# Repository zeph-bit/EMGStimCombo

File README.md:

# EMGStimCombo
Stackable sEMG and TENS combination device.

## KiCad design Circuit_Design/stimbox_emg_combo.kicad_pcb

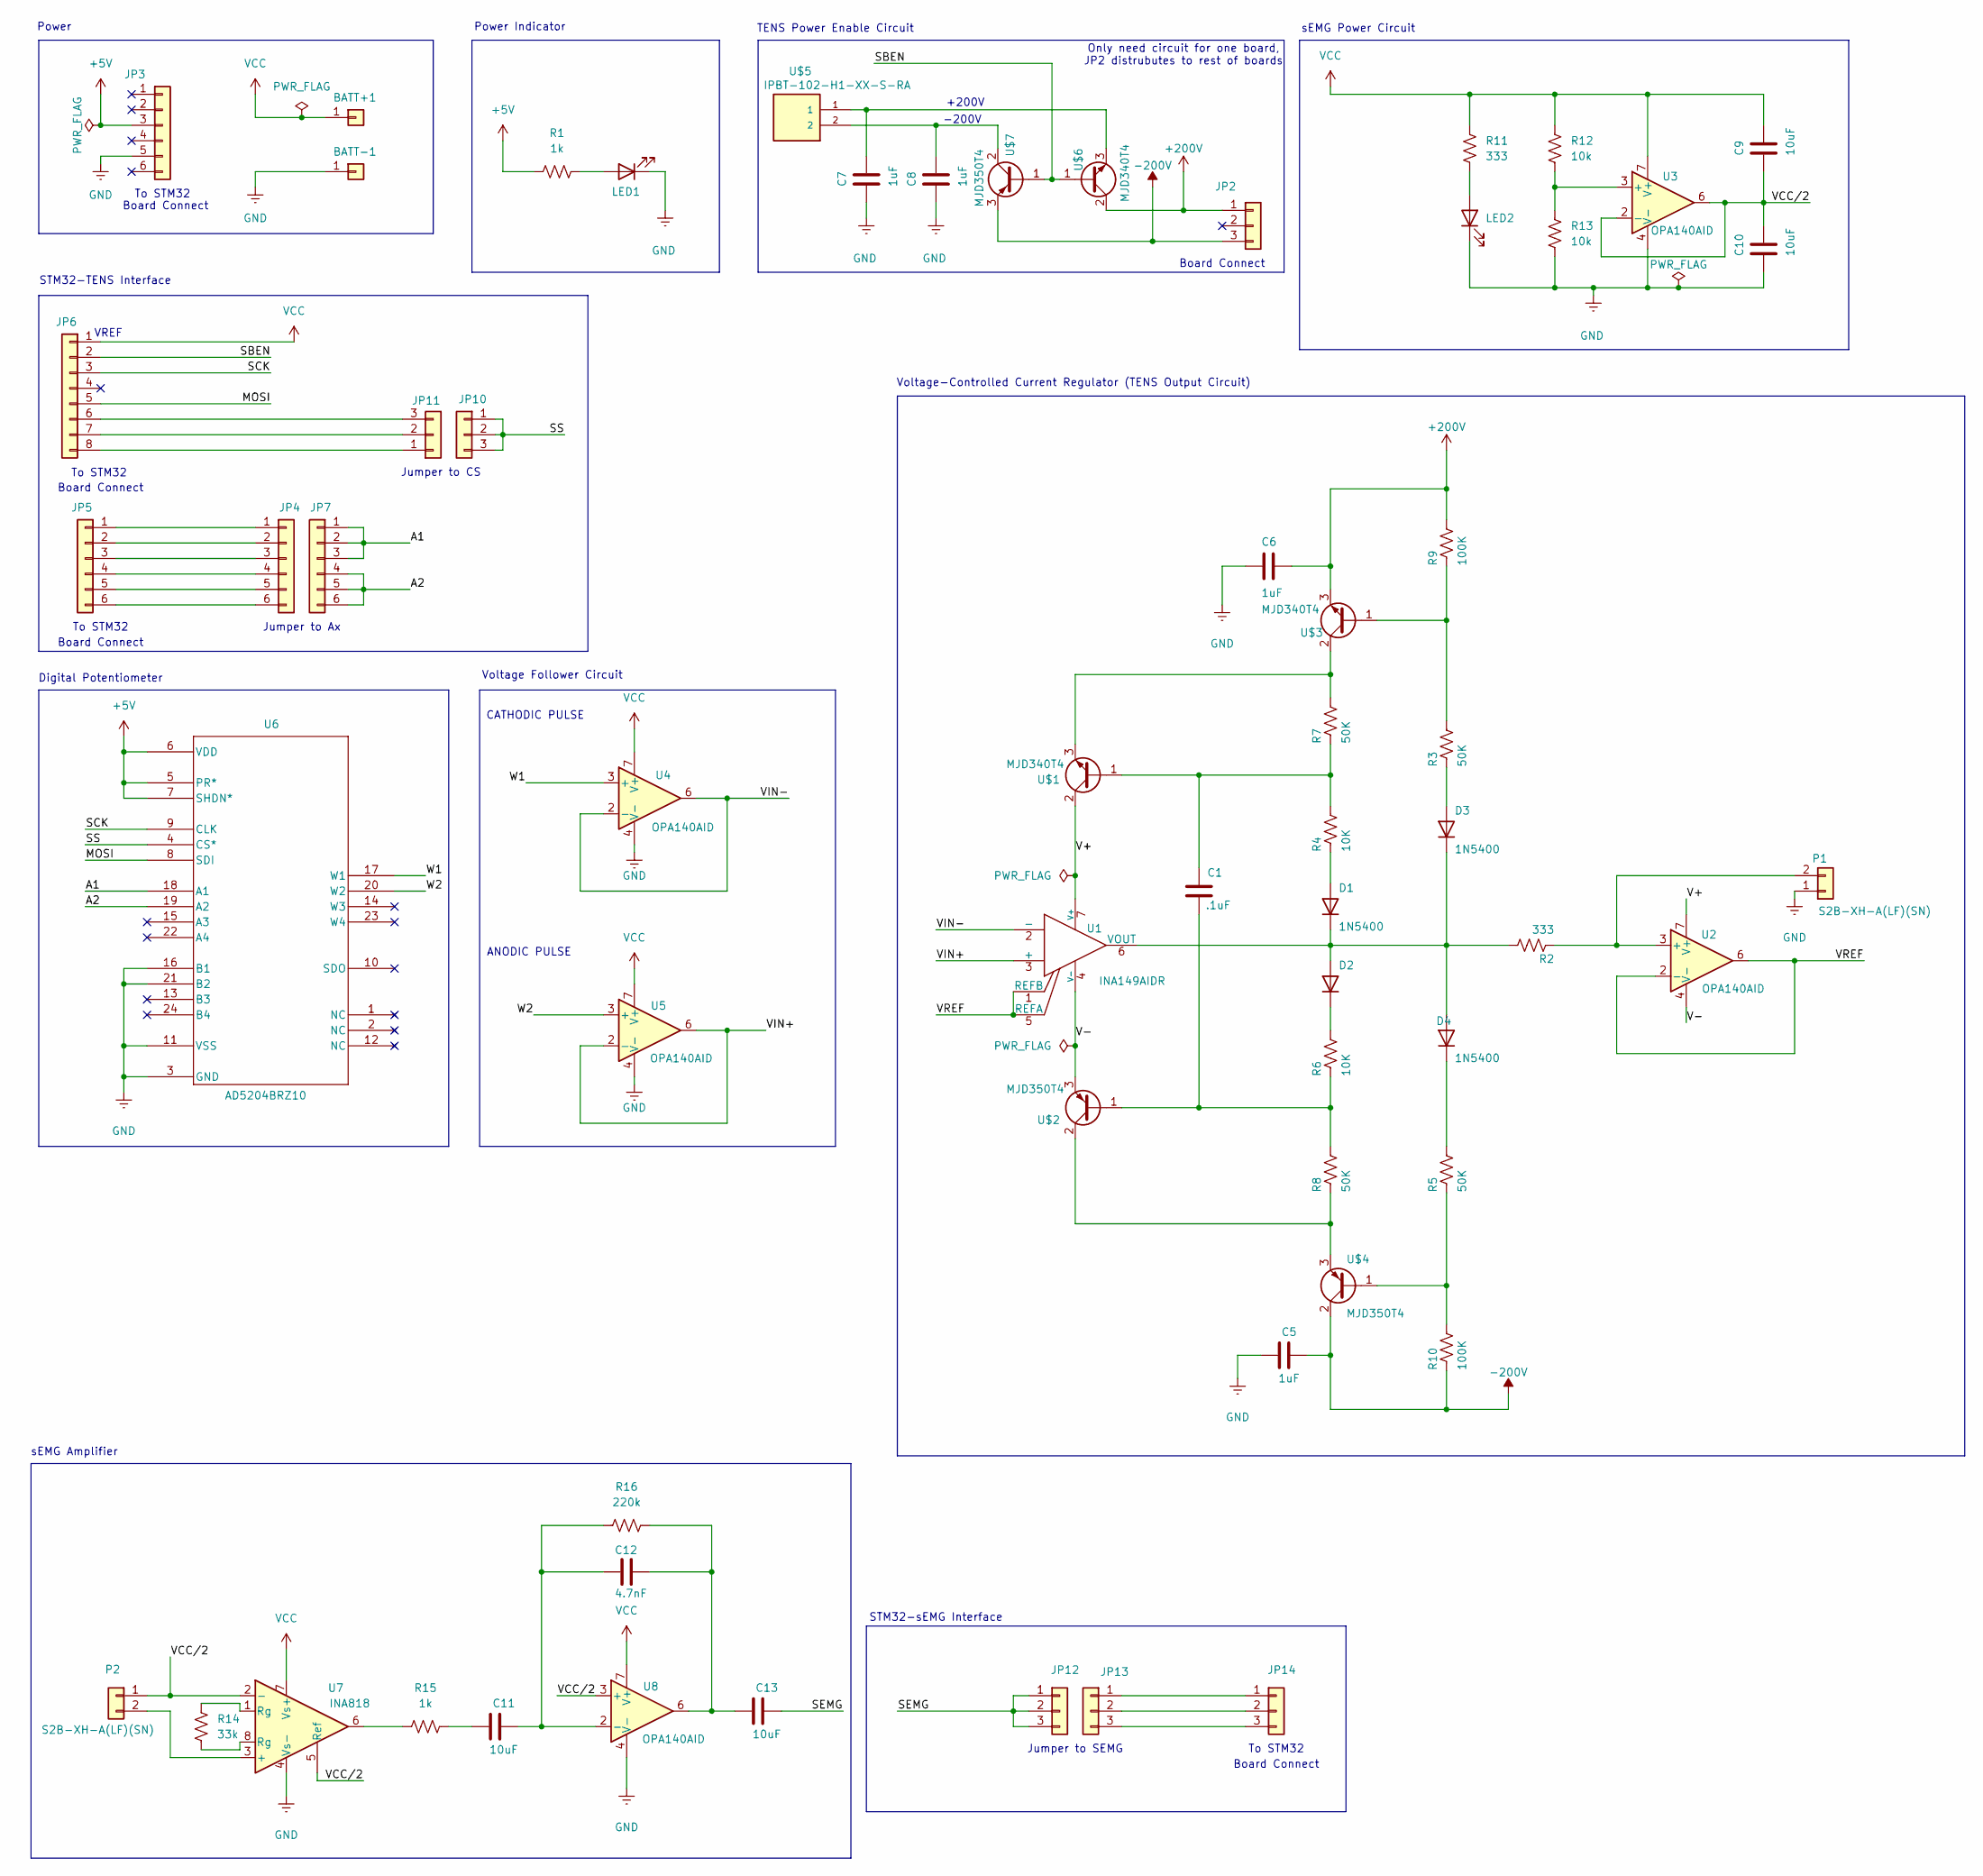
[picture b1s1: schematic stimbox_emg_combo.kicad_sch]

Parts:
BATT+1: PINHD-1X1; PinHeader_1x01_P2.54mm_Vertical
BATT-1: PINHD-1X1; PinHeader_1x01_P2.54mm_Vertical
C1: .1uF; C_1206_3216Metric
C5, C6, C7, C8: 1uF; C_2220_5750Metric
C9, C10, C11, C13: 10uF; C_2220_5750Metric
C12: 4.7nF; C_2220_5750Metric
D1, D2, D3, D4: 1N5400; D_DO-201AD_P15.24mm_Horizontal
JP2, JP14: PINHD-1X3-STACK; PinSocket_1x03_P2.54mm_Vertical
JP3: PINHD-1X6-STACK; PinSocket_1x02_P2.54mm_Vertical
JP4, JP7: PINHD-1X6; PinHeader_1x06_P2.54mm_Vertical
JP5: PINHD-1X6-STACK; PinSocket_1x06_P2.54mm_Vertical
JP6: PINHD-1X8-STACK; PinSocket_1x08_P2.54mm_Vertical
JP10, JP11, JP12, JP13: PINHD-1X3; PinHeader_1x03_P2.54mm_Vertical
LED1, LED2: LEDCHIPLED_1206; LED_1206_3216Metric
P1, P2: S2B-XH-A(LF)(SN); JST_XH_S2B-XH-A_1x02_P2.50mm_Horizontal; DIGI-KEY_PART_NUMBER 455-2257-ND
R1, R15: 1k; R_0805_2012Metric
R2, R11: 333; R_1206_3216Metric
R3, R5, R7, R8: 50K; R_1206_3216Metric
R4, R6: 10K; R_1206_3216Metric
R9, R10: 100K; R_1206_3216Metric
R12, R13: 10k; R_1206_3216Metric
R14: 33k; R_1206_3216Metric
R16: 220k; R_1206_3216Metric
U1: INA149AIDR; D0008A_L
U2, U3, U4, U5, U8: OPA140AID; SOIC-8_3.9x4.9mm_P1.27mm
U6: AD5204BRZ10; RW_24_ADI; DIGI-KEY_PART_NUMBER AD5204BRZ100-ND
U7: INA818; SOIC-8_TEX
U$1, U$3, U$6: MJD340T4; TO-252_6P6X6P2X2P25_STM
U$2, U$4, U$7: MJD350T4; TO-252_6P6X6P2X2P25_STM
U$5: IPBT-102-H1-XX-S-RA

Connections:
+3.3V: JP3.2
+5V: JP3.3, R1.1, U6.5 (PR*), U6.6 (VDD), U6.7 (SHDN*)
/A1: JP7.1, JP7.2, JP7.3, U6.18 (A1)
/A2: JP7.4, JP7.5, JP7.6, U6.19 (A2)
/MOSI: JP6.5, U6.8 (SDI)
/SBEN: JP6.2, U$6.1 (B), U$7.1 (B)
/SCK: JP6.3, U6.9 (CLK)
/SEMG: C13.2, JP12.1, JP12.2, JP12.3
/SS: JP10.1, JP10.2, JP10.3, U6.4 (CS*)
/V+: U1.7 (V+), U2.7 (V+), U$1.2 (C)
/V-: U1.4 (V-), U2.4 (V-), U$2.3 (E)
/VCC/2: C9.1, C10.2, P2.1, U3.2 (-), U3.6, U7.2 (-), U7.5 (Ref), U8.3 (+)
/VIN+: U1.3 (+), U5.2 (-), U5.6
/VIN-: U1.2 (-), U4.2 (-), U4.6
/VREF: U1.1 (REFB), U1.5 (REFA), U2.2 (-), U2.6
/W1: U4.3 (+), U6.17 (W1)
/W2: U5.3 (+), U6.20 (W2)
GND: BATT-1.1 (Pin_1_1), C5.1, C6.1, C7.1, C8.1, C10.1, JP3.5, LED1.1 (K), LED2.1 (K), P1.1, R13.2, U3.4 (V-), U4.4 (V-), U5.4 (V-), U6.3 (GND), U6.11 (VSS), U6.16 (B1), U6.21 (B2), U7.4 (Vs-), U8.4 (V-)
unnamed: C11.1, R15.2
unnamed: C12.2, C13.1, R16.2, U8.6
unnamed: D1.2 (A), R4.2
unnamed: D1.1 (K), D2.2 (A), D3.1 (K), D4.2 (A), R2.1, U1.6 (VOUT)
unnamed: D2.1 (K), R6.1
unnamed: D3.2 (A), R3.2
unnamed: D4.1 (K), R5.1
unnamed: JP4.1, JP5.1
unnamed: JP4.2, JP5.2
unnamed: JP4.3, JP5.3
unnamed: JP4.4, JP5.4
unnamed: JP4.5, JP5.5
unnamed: JP4.6, JP5.6
unnamed: JP6.8, JP11.1
unnamed: JP6.7, JP11.2
unnamed: JP6.6, JP11.3
unnamed: JP13.1, JP14.1
unnamed: JP13.2, JP14.2
unnamed: JP13.3, JP14.3
unnamed: LED1.2 (A), R1.2
unnamed: LED2.2 (A), R11.2
unnamed: P1.2, R2.2, U2.3 (+)
unnamed: P2.2, U7.3 (+)
unnamed: R14.1, U7.1 (Rg)
unnamed: R14.2, U7.8 (Rg)
unnamed: R15.1, U7.6
unnamed: R12.2, R13.1, U3.3 (+)
unnamed: C11.2, C12.1, R16.1, U8.2 (-)
unnamed: C1.1, R4.1, R7.2, U$1.1 (B)
unnamed: R7.1, U$1.3 (E), U$3.2 (C)
unnamed: C1.2, R6.2, R8.1, U$2.1 (B)
unnamed: R8.2, U$2.2 (C), U$4.3 (E)
unnamed: R3.1, R9.2, U$3.1 (B)
unnamed: R5.2, R10.1, U$4.1 (B)
unnamed: C7.2, U$5.1, U$6.3 (E)
unnamed: C8.2, U$5.2, U$7.2 (C)
VCC: BATT+1.1 (Pin_1_1), C9.2, JP6.1, R11.1, R12.1, U3.7 (V+), U4.7 (V+), U5.7 (V+), U7.7 (Vs+), U8.7 (V+)

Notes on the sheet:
To STM32
Only need circuit for one board, JP2 distrubutes to rest of boards
Board Connect
Jumper to SEMG
STM32-sEMG Interface
TENS Power Enable Circuit
Jumper to CS
-200V
Jumper to Ax
+200V
VREF
sEMG Power Circuit
Power
Voltage Follower Circuit
ANODIC PULSE
Voltage-Controlled Current Regulator (TENS Output Circuit)
sEMG Amplifier
CATHODIC PULSE
Digital Potentiometer
Power Indicator
STM32-TENS Interface

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
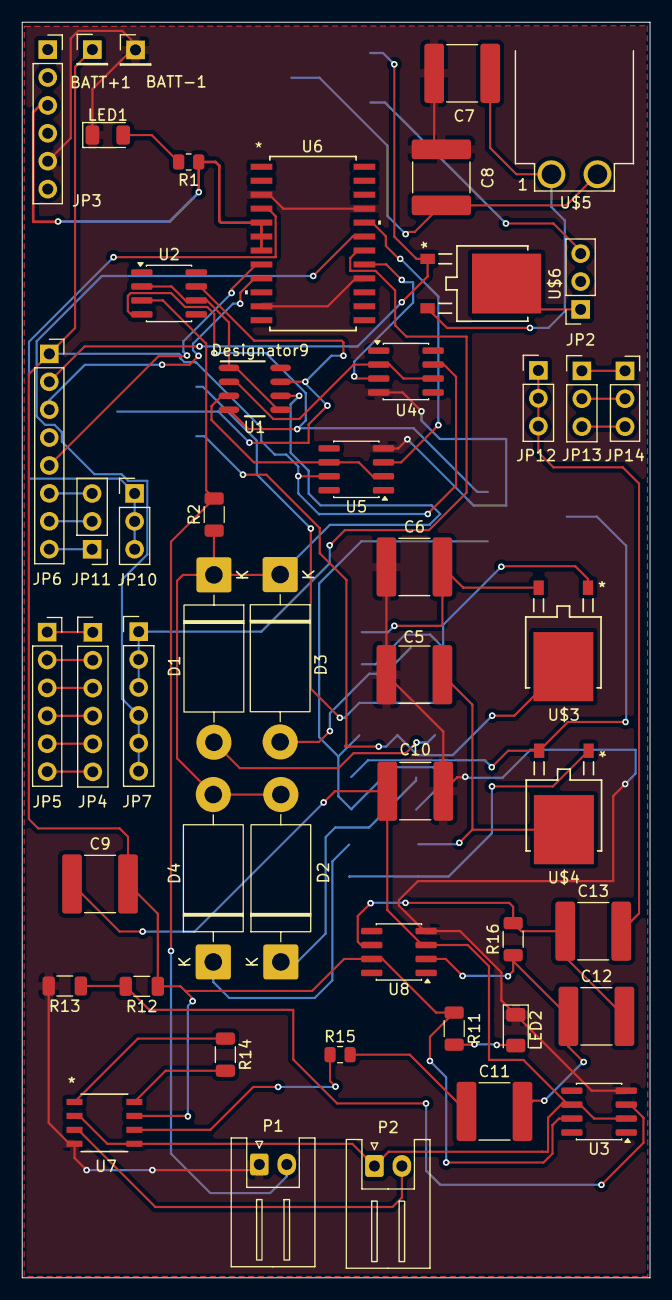
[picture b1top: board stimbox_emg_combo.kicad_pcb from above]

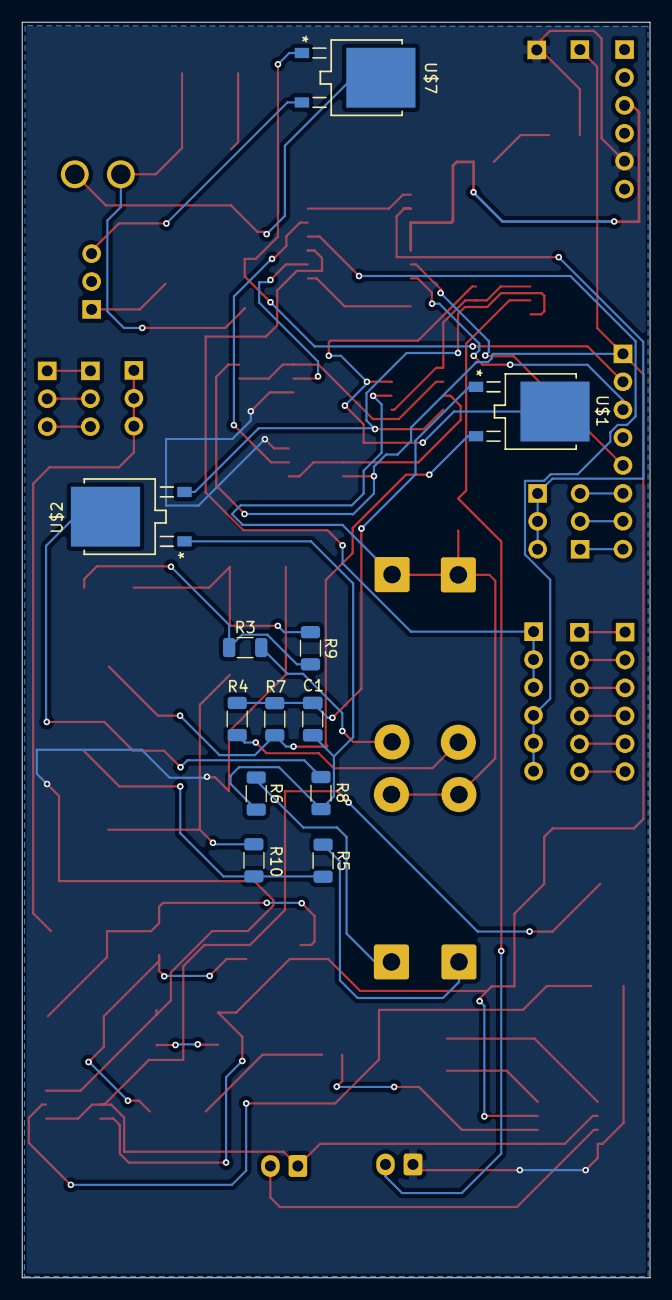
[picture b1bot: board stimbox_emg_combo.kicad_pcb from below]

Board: 2 copper layers, 57.2 x 114.3 mm, 62 parts (12 on the bottom side), 58 nets.

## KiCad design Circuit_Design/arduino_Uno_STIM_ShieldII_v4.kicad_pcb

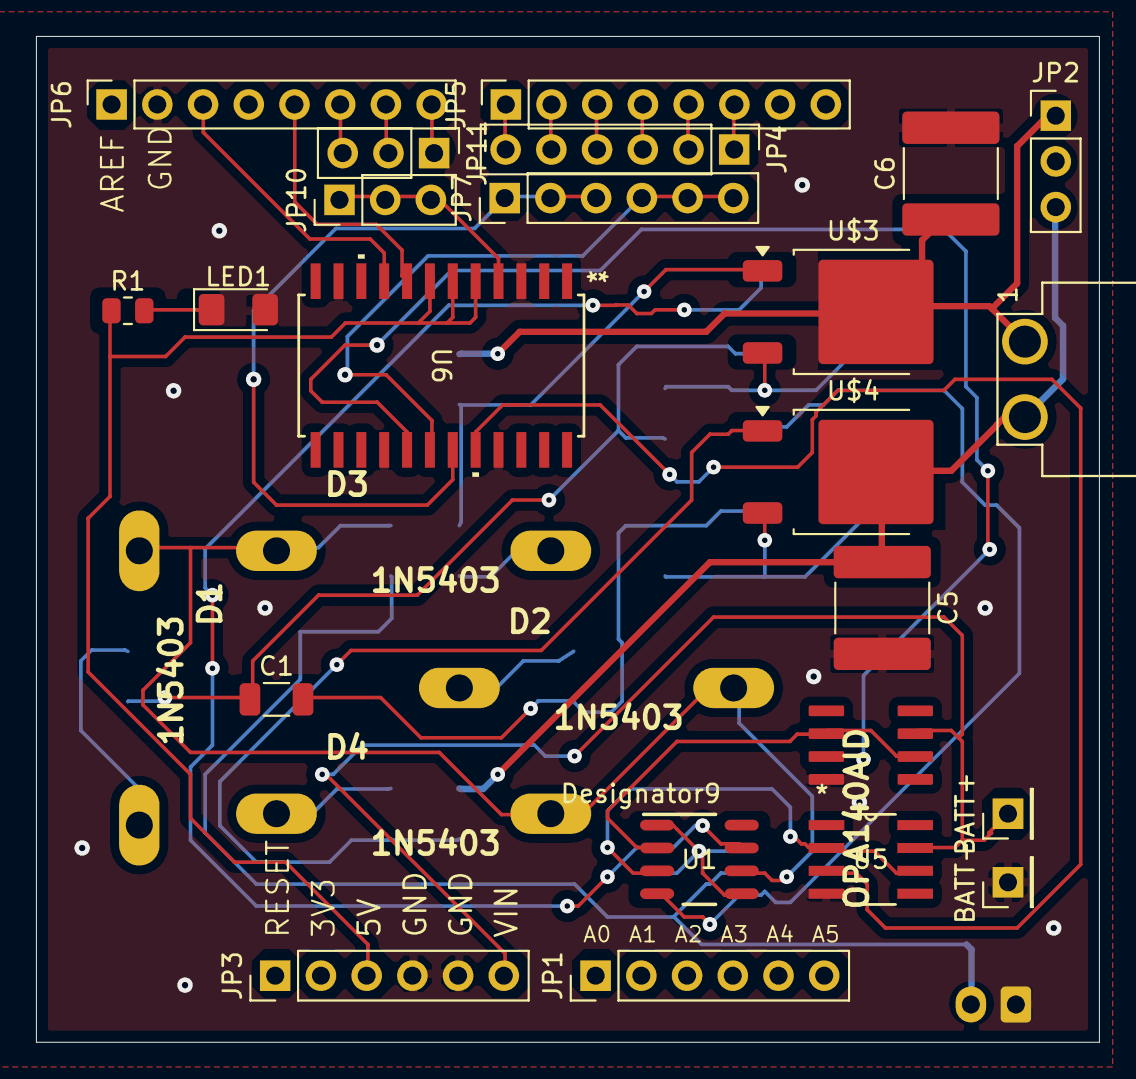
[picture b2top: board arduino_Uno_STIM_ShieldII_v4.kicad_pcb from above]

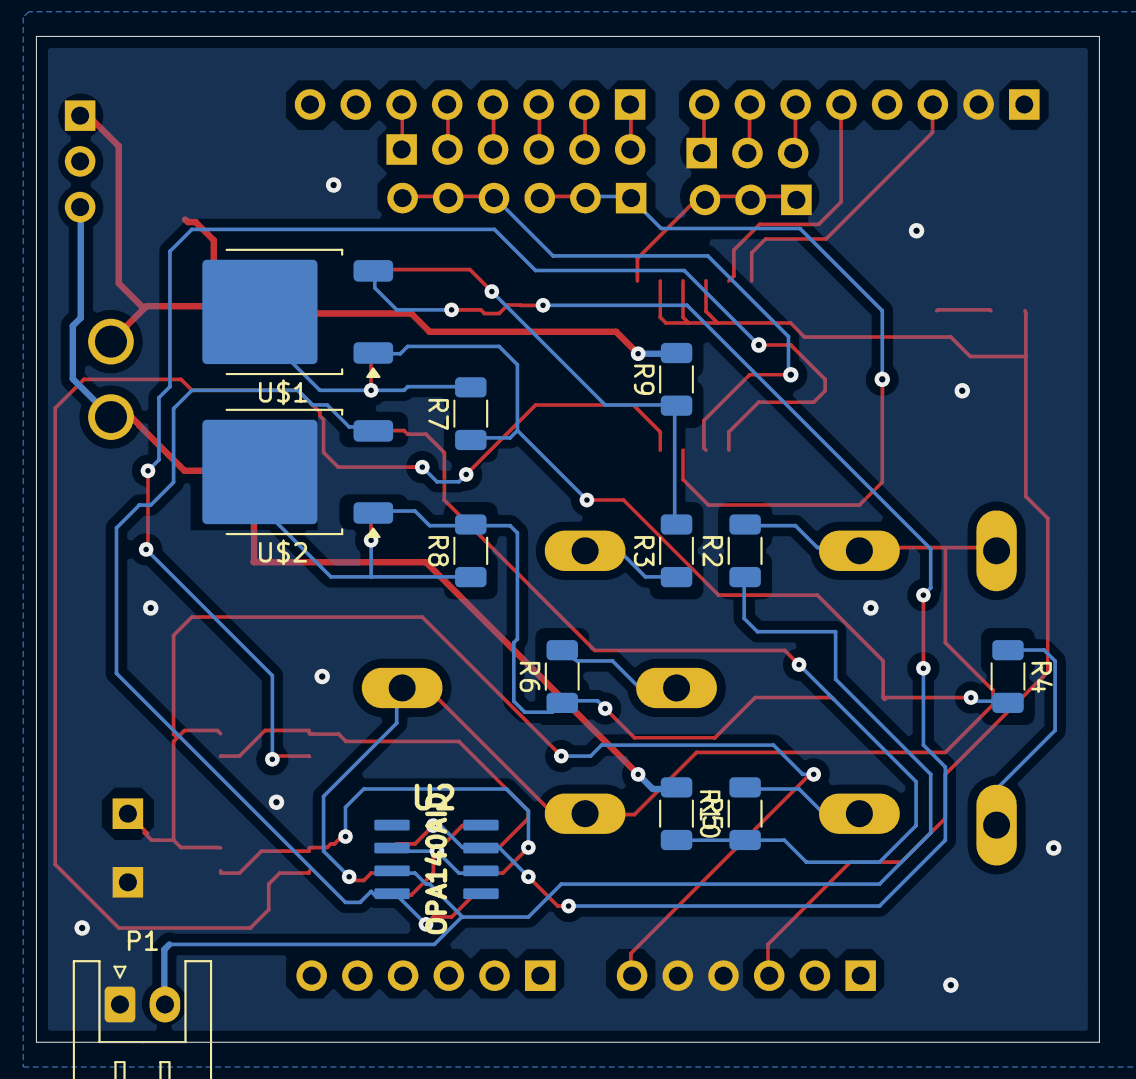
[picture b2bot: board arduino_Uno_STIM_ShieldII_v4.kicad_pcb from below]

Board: 2 copper layers, 59.1 x 55.9 mm, 40 parts (13 on the bottom side), 39 nets.

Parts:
BATT+: PinHeader_1x01_P2.54mm_Vertical
BATT-: PinHeader_1x01_P2.54mm_Vertical
C1: ${1UF}; C_1206_3216Metric
C5, C6: 1uF; C_2220_5750Metric
D1, D2, D3, D4: 1N5403; DO201-15
JP1, JP3, JP4, JP7: PinHeader_1x06_P2.54mm_Vertical
JP2, JP10, JP11: PinHeader_1x03_P2.54mm_Vertical
JP5, JP6: PinSocket_1x08_P2.54mm_Vertical
LED1: LED_1206_3216Metric_Pad1.42x1.75mm_HandSolder
P1: S2B-XH-A(LF)(SN); JST_XH_S2B-XH-A_1x02_P2.50mm_Horizontal
R1: 1k; R_0805_2012Metric
R2: 333; R_1206_3216Metric
R3, R5, R7, R8: 50K; R_1206_3216Metric
R4, R6: 10K; R_1206_3216Metric
R9, R10: 100K; R_1206_3216Metric
U1: INA149AIDR; D0008A_L
U2: SOIC127P599X175-8N
U4: OPA140AID; SOIC127P599X175-8N
U5: D8
U6: AD5204BRZ10; RW_24_ADI
U$1, U$3: MJD340T4; TO-252-2
U$2, U$4: MJD350T4; TO-252-2
U$5: IPBT-102-H1-XX-S-RA

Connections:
9V: BATT+.1, JP3.6, U4.7, U5.7
+5V: JP3.3, R1.1, U6.5, U6.6, U6.7
+200V: C6.1, JP2.1, R9.2, U$5.1
-200V: C5.1, JP2.3, R10.1, U$5.2
GND: BATT-.1, C5.2, C6.2, JP3.4, JP3.5, JP6.2, LED1.2, P1.1, U4.4, U5.4, U6.3, U6.11, U6.16, U6.21
IO2: JP4.1, JP5.6
IO3: JP4.2, JP5.5
IO4: JP4.3, JP5.4
IO5: JP4.4, JP5.3
IO6: JP4.5, JP5.2
IO7: JP4.6, JP5.1
IO8: JP6.8, JP11.1
IO9: JP6.7, JP11.2
IO10: JP6.6, JP11.3
MOSI: JP6.5, U6.8
unnamed: D1.C, D2.A, D3.C, D4.A, R2.2, U1.6
unnamed: D3.A, R3.1
unnamed: LED1.1, R1.2
unnamed: JP7.4, JP7.5, JP7.6, U6.18
unnamed: JP7.1, JP7.2, JP7.3, U6.19
unnamed: D1.A, R4.1
unnamed: P1.2, R2.1, U2.3
unnamed: D4.C, R5.2
unnamed: D2.C, R6.2
unnamed: C1.2, R6.1, R8.2, U$2.1
unnamed: C1.1, R4.2, R7.1, U$1.1
unnamed: R7.2, U$3.3
unnamed: R8.1, U$2.2, U$4.3
unnamed: R3.2, R9.1, U$3.1
unnamed: R5.1, R10.2, U$4.1
unnamed: U1.1, U1.5, U2.2, U2.6
SCK: JP6.3, U6.9
SS: JP10.1, JP10.2, JP10.3, U6.4
V+: U1.7, U2.7, U$1.3
V-: U1.4, U2.4, U$2.3
VIN+: U1.3, U5.2, U5.6
VIN-: U1.2, U4.2, U4.6
W1: U4.3, U6.17
W2: U5.3, U6.20

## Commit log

2026-05-09 Adding gerber files.
2026-05-09 Adding KiCAD models.
2026-05-09 Adding additional circuit files.
